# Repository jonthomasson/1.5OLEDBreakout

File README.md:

# 1.5OLEDBreakout
1.5" OLED Breakout SSD1351

Who doesn't love OLED's? Their relatively low power requirements as well as vibrant color displays are alluring to the hacker. While working on a few projects recently I had the need to interface with one of these OLED displays. There didn't seem to be any breakout boards that broke out the parallel interface pins of the controller, so I decided to make my own.

Scouring the internet for a decent OLED display, I came across this one from buydisplay.com. It's a 128x128 RGB display, with 1.5" diagonal measurement. The controller, SSD1351, supports a 8, 16, or 18 bit parallel interface, as well as SPI for communications. It seemed perfect for the projects I had in mind. Most breakout boards out there only take advantage of the SPI pins of the controller, and at least one of my projects would require access to the parallel interface, so I decided to just build my own board to suite my needs. Hopefully someone else finds it useful.

After tying BS0 and BS1 to ground to enable SPI, I tested the OLED with the [adafruit  SSD1351 driver library](https://github.com/adafruit/Adafruit-SSD1351-library).

![OLED Breakout running test program from Adafruit SSD1351 library](https://lh3.googleusercontent.com/MsKkN0FBhNv1MBZHOAWehuTeS2_8jIe-vTxg2sqLBS44pNBJPy4iuyDUc9Usf4BQjBpzPWWo7Bnqe3NkQCG8paahzHArL8N2OJRp6vAqdoAcOqIph1lTVyudKYCDfX7VTnMsb4jkWHEpYea2pUTW6P7bMah0QvajGr9Vv_Ka1nz8VvwMx_XcXBHSA8MVLC4mheWbWq2etjKzS0w7jgDfSmGsj1dWxFcMfnDJYUARnoZf_Ecu_VUkCVuFhfB3bfooKdvGITS8FaRpiiIor4YhDutwE9h8ZXBRsJ0EaRE9oovJ_CZIdYoFb1mrJiMMzbZo_m1NONMx31lA0AtXVxDD3_TSAVwcc_2xc-_wRHR5UxiRDyMdHFiY_l0dUZIc7PXVY9yiFTdeTccjxLrm2XppLVS5QKP7OgbR_IOFpHCrpZ6-vbgaLmIw-qbnifM7X68Q8axLn03WRp7NhK2jvG_d8vboeV-OaZebjD-bPcUK_6cenOedzorvjP1qjMNFs7BaMNp_RFqAtlz56_IL618pNLowKLZ3Uh-RCuQk9Qy1iAJN5mOoGUT4JS21LYV82Z59FOqgL9iSNJIoaGaWEbZlrih909cDvEl6fb_3MQ4k=w1688-h949-no)

![enter image description here](https://lh3.googleusercontent.com/N4O0tLOCn0Eo37ZxnNt6EblDyE1QjhN_yxB5joiKvIgpHKnZqY0Tt5LPPp8S8s6vpi8v4A9ziG02BMIxa5gTNILQGj3B6yaHgSGacTQC9WjqcnNdZdKckPPqEXiD1Bdt_oRc85JqJZIHr91pL3aQS7A8h610xYnENwIUSkq75CgIYe2bPRbvZ_B09w-lDonRjTYo7xuQ_842ufJOjFXs10Rznar2i5o7Cc5IxF0kcFH1wVu8sHFTCEm_xffTFr8UgDPmG-y94f-umWpQks5XLWrhS6qLWHBYn4ED8aYl1b2wHeDXSp1CXR3UVtDq5sChqppDEJJUfjohhNUl4RfgfJebFzFZR6ZVvmNS3mhxa7NHj9fORLQlyYdXboQTziLBcRMhZDKCvBUCDJ3TQCTlVttUPPMoPq4F5qaboPdrU_tSyGRhDdRTijBlBIn3xsylU8Ip844YMhsJtS_O6xY9tNjXKBb7gK3YVKy-qaMtF4O1Z26QXzV2yLqy29ZDMwsqhQKAy-5qafAfvoEdfoSLm69EmFEEJ4fB6paoH-9Wn0k8a7aUpfmgh1wDXKqv0JxGyFew9EZ3R-GR-hWV9tqFCL4f2KFu_bQE072QgY-5=w1079-h607-no)

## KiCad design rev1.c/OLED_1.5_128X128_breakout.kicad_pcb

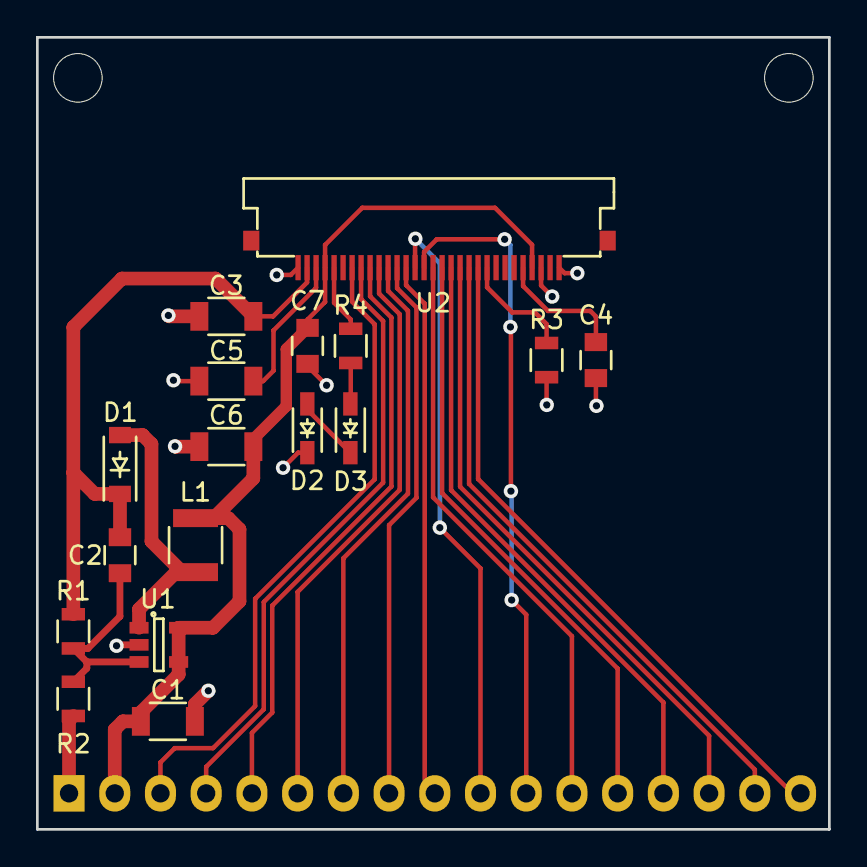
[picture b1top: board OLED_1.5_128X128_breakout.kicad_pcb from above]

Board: 2 copper layers, 44.0 x 44.0 mm, 18 parts (1 on the bottom side), 26 nets.

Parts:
C1, C3, C5, C6: 10uF; C_1206
C2: .1uF; C_0805
C4, C7: 1uF; C_0805
D1: BAT54T1G; SOD-123
D2, D3: 1N4148; SOD-323
L1: 10uH; C_1210
P1: BREAKOUT; Pin_Header_Angled_1x17
R1: 100K; R_0805
R2: 10K; R_0805
R3: 600K; R_0805
R4: 50; R_0805
U1: FAN5331SX; SOT-23-5
U2: ER_OLED015_1C; CONNECTORS_FPC_SFV30R_4STBE1HLF

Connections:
/+3V3: C1.1, C6.1, C7.1, L1.1, P1.2, U1.4, U1.5, U2.4, U2.27
/+13V: C2.1, C3.1, D1.1, R1.1, U2.2
/BS0: P1.13, U2.17
/BS1: P1.14, U2.18
/CS#: P1.15, U2.19
/D0/SCK: P1.10, U2.14
/D1/SDIN: P1.9, U2.13
/D2: P1.8, U2.12
/D3: P1.7, U2.11
/D4: P1.6, U2.10
/D5: P1.5, U2.9
/D6: P1.4, U2.8
/D7: P1.3, U2.7
/D/C#: P1.16, U2.20
/E/RD#: P1.11, U2.15
/R/W#: P1.12, U2.16
/RES#: P1.17, U2.21
GND: C1.2, C3.2, C4.2, C5.2, C6.2, C7.2, D2.1, P1.1, R2.2, R3.2, U1.2, U2.1, U2.28, U2.30
unnamed: C2.2, R1.2, R2.1, U1.3
unnamed: C4.1, U2.26
unnamed: C5.1, U2.3
unnamed: D1.2, L1.2, U1.1
unnamed: D2.2, D3.1
unnamed: D3.2, R4.2
unnamed: R3.1, U2.22
unnamed: R4.1, U2.5

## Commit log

2017-04-23 :tada: Added .gitattributes & .gitignore files
2017-04-23 initial checkin
2017-04-25 added rev 1.b with better routing around L1.
2017-10-01 fixing connector
2017-10-03 finished routing rev 1.c
2017-10-03 finished silk screen and created gerbers
2017-10-03 efficiency check and new gerbers
2018-02-09 added firmware
